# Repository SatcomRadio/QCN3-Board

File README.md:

# QCN3-Board

PCB board for the hybrid coupler QCN3

## Warning, maximum transmission power (datasheet) is 15W. But it's better to not go over 5-10W

It allows to do the right hand circular polarization without having to deal with coax cables.  

------

Nano VNA results (with 2 50 ohms loads at the outputs)

------

Connect the 90º pin to the right of the 0º pin to allow **right hand circular polarization**.  
Make sure that the 2 output wires have the same length!

------

You can order it at jlcpcb or other companies using the gerber zip file in this repository.  
Make sure to order it with 1.6 board width  

------

BOM:

- 1x QCN-3
- 2x SMD resistor 2512 100Ω 2W
- 3x SMA connectors for PCB with 1.6mm spacing

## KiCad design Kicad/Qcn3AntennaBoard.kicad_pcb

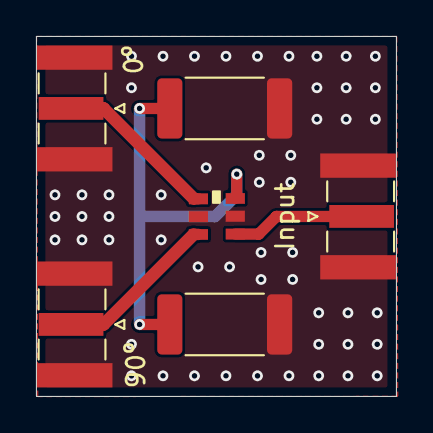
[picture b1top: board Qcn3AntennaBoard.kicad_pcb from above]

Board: 2 copper layers, 20.0 x 20.0 mm, 6 parts (0 on the bottom side), 5 nets.

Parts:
0º, 90º: Conn_Coaxial_Small; SMA_Samtec_SMA-J-P-X-ST-EM1_EdgeMount
Input: Conn_Coaxial_Small; SMA_Samtec_SMA-J-P-X-ST-EM1_EdgeMount
R1, R2: 100; R_2512_6332Metric_Pad1.40x3.35mm_HandSolder
U1: QCN3

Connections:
GND: 0º.2 (Ext), 90º.2 (Ext), Input.2 (Ext), R1.2, R2.2, U1.2 (GND), U1.5 (GND)
unnamed: 0º.1 (In), U1.4 (P1)
unnamed: 90º.1 (In), U1.6 (P2)
unnamed: Input.1 (In), U1.1 (SUM)
unnamed: R1.1, R2.1, U1.3 (50_OHM)
